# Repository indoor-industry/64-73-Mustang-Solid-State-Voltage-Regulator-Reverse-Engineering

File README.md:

A reverse engineering of the Darlington transistor based solid-state replacements for old Mustangs voltage regulators that are commonly sold as spares. 
The KiCAD project includes a schematic and a PCB with gerber files ready for production, all components are specified on the silkscreen.
These voltage regulators are not very good though, this was done out of curiosity, not necessity.

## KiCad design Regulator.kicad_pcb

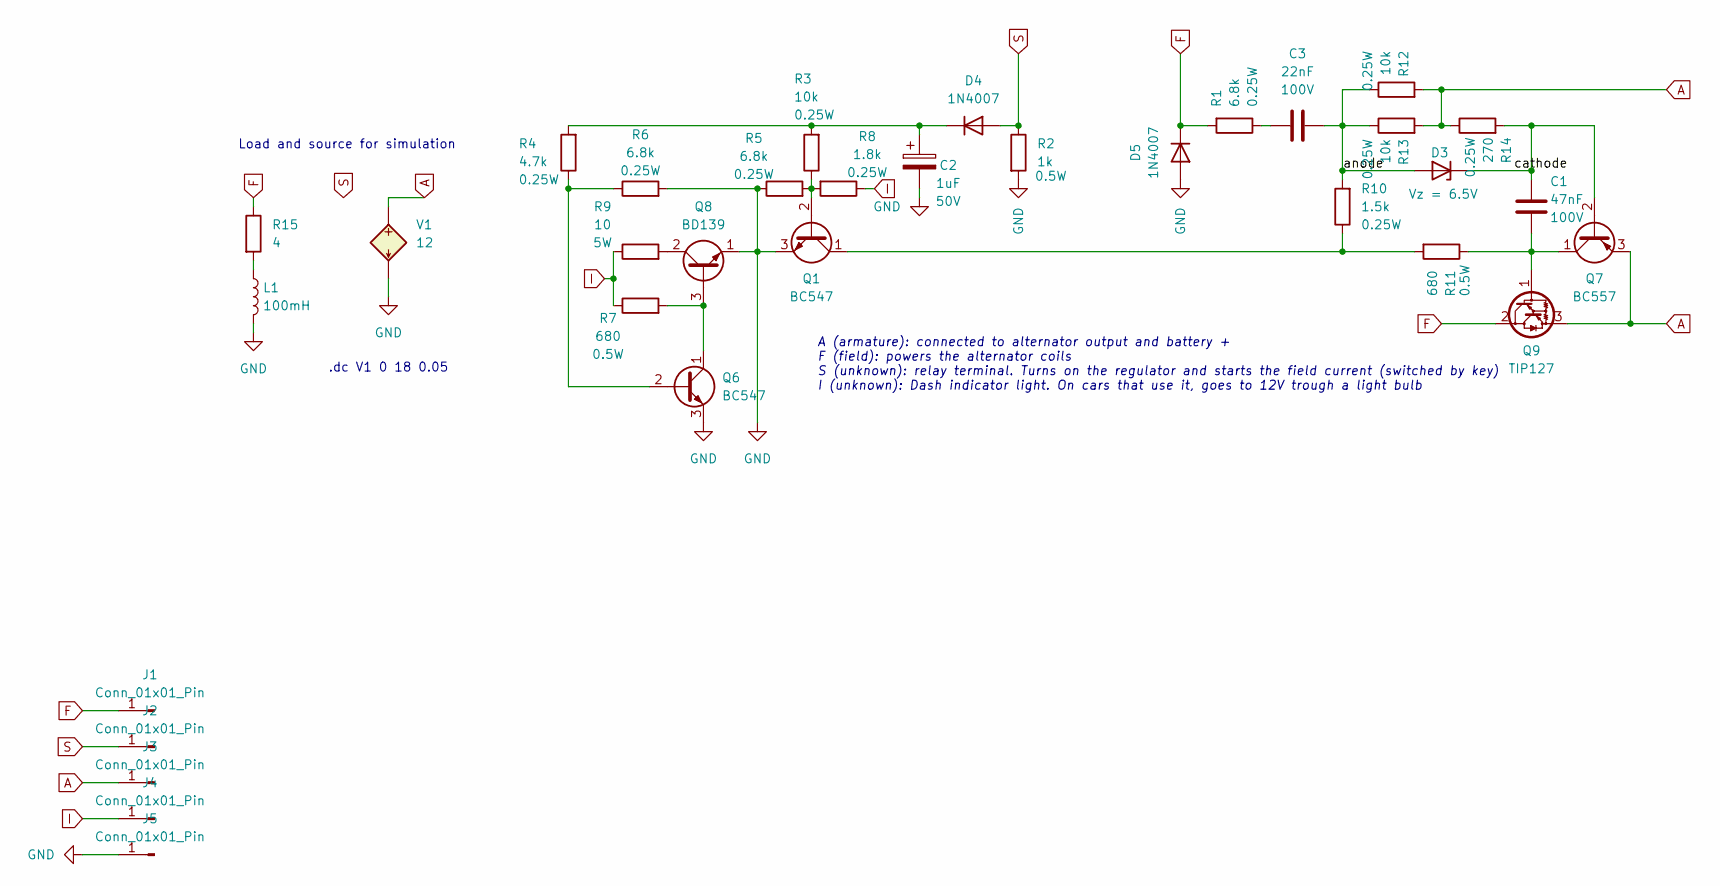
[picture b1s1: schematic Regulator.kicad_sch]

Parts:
C1: 47nF; C_Rect_L7.0mm_W2.5mm_P5.00mm
C2: 1uF; CP_Radial_D4.0mm_P2.00mm
C3: 22nF; C_Rect_L7.0mm_W2.5mm_P5.00mm
D3: Vz = 6.5V; D_A-405_P7.62mm_Horizontal
D4, D5: 1N4007; D_DO-41_SOD81_P10.16mm_Horizontal
J1, J2, J3, J4, J5: Conn_01x01_Pin; SolderWire-6sqmm_1x01_D3.5mm_OD7mm
L1: 100mH
Q1, Q6: BC547; TO-92_Inline
Q7: BC557; TO-92_Inline
Q8: BD139; TO-126-3_Vertical
Q9: TIP127; TO-220-3_Vertical
R1, R5, R6: 6.8k; R_Axial_DIN0207_L6.3mm_D2.5mm_P10.16mm_Horizontal
R2: 1k; R_Axial_DIN0309_L9.0mm_D3.2mm_P15.24mm_Horizontal
R3, R12, R13: 10k; R_Axial_DIN0207_L6.3mm_D2.5mm_P10.16mm_Horizontal
R4: 4.7k; R_Axial_DIN0207_L6.3mm_D2.5mm_P10.16mm_Horizontal
R7, R11: 680; R_Axial_DIN0309_L9.0mm_D3.2mm_P15.24mm_Horizontal
R8: 1.8k; R_Axial_DIN0207_L6.3mm_D2.5mm_P10.16mm_Horizontal
R9: 10; R_Axial_DIN0516_L15.5mm_D5.0mm_P20.32mm_Horizontal
R10: 1.5k; R_Axial_DIN0207_L6.3mm_D2.5mm_P10.16mm_Horizontal
R14: 270; R_Axial_DIN0207_L6.3mm_D2.5mm_P10.16mm_Horizontal
R15: 4
V1: 12

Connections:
/anode: C3.2, D3.2 (A), R10.2, R12.1, R13.1
/cathode: C1.1, D3.1 (K), Q7.2 (B), R14.2
A: J3.1, Q7.3 (E), Q9.3 (E), R12.2, R13.2, R14.1, V1.1 (N+)
F: D5.1 (K), J1.1, Q9.2 (C), R1.2, R15.1
GND: C2.2, D5.2 (A), J5.1, L1.2, Q1.3 (E), Q6.3 (E), Q8.1 (E), R2.2, R5.1, R6.2, V1.2 (N-)
I: J4.1, R7.1, R8.1, R9.1
unnamed: C3.1, R1.1
unnamed: C2.1, D4.1 (K), R3.2, R4.2
unnamed: L1.1, R15.2
unnamed: Q1.2 (B), R3.1, R5.2, R8.2
unnamed: Q1.1 (C), R10.1, R11.2
unnamed: Q6.2 (B), R4.1, R6.1
unnamed: Q6.1 (C), Q8.3 (B), R7.2
unnamed: C1.2, Q7.1 (C), Q9.1 (B), R11.1
unnamed: Q8.2 (C), R9.2
S: D4.2 (A), J2.1, R2.1

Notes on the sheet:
A (armature): connected to alternator output and battery + F (field): powers the alternator coils S (unknown): relay terminal. Turns on the regulator and starts the field current (switched by key) I (unknown): Dash indicator light. On cars that use it, goes to 12V trough a light bulb
Load and source for simulation
.dc V1 0 18 0.05

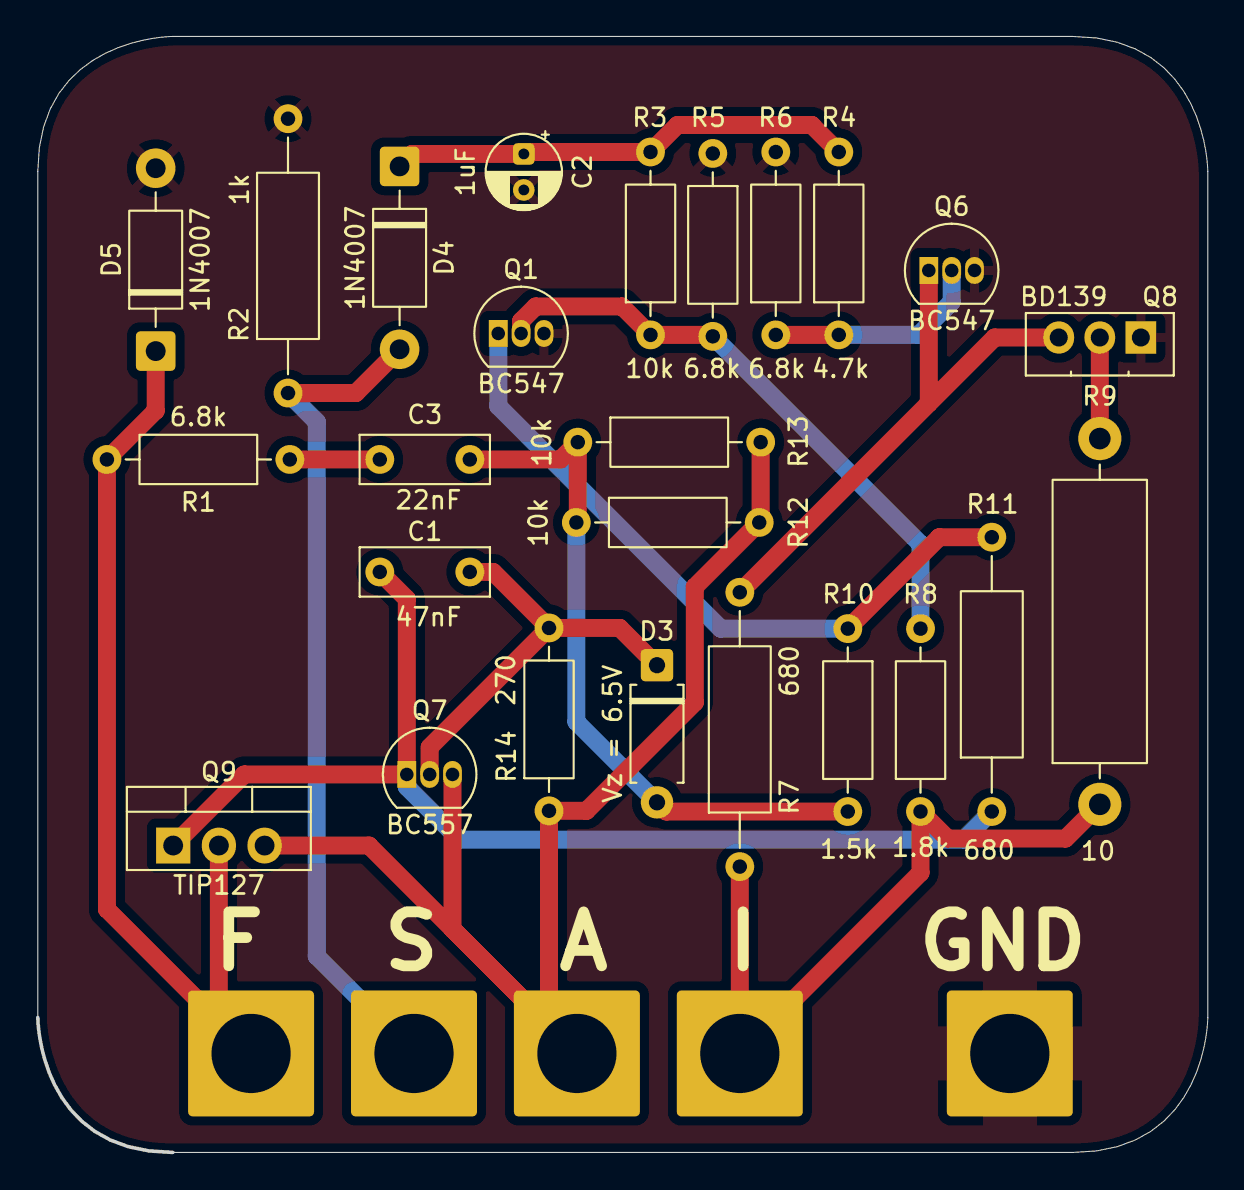
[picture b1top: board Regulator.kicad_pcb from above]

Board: 2 copper layers, 65.0 x 62.0 mm, 30 parts (0 on the bottom side), 15 nets.

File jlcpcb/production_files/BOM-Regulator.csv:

Comment,Designator,Footprint,LCSC,Quantity
BC557,Q7,TO-92_Inline,,1
10k,R3,R_Axial_DIN0207_L6.3mm_D2.5mm_P10.16mm_Horizontal,,1
BC547,Q1,TO-92_Inline,,1
1uF,C2,CP_Radial_D4.0mm_P2.00mm,,1
10k,R13,R_Axial_DIN0207_L6.3mm_D2.5mm_P10.16mm_Horizontal,,1
Conn_01x01_Pin,J1,SolderWire-6sqmm_1x01_D3.5mm_OD7mm,,1
1.8k,R8,R_Axial_DIN0207_L6.3mm_D2.5mm_P10.16mm_Horizontal,,1
Conn_01x01_Pin,J3,SolderWire-6sqmm_1x01_D3.5mm_OD7mm,,1
Vz = 6.5V,D3,D_A-405_P7.62mm_Horizontal,,1
TIP127,Q9,TO-220-3_Vertical,,1
BD139,Q8,TO-126-3_Vertical,,1
680,R7,R_Axial_DIN0309_L9.0mm_D3.2mm_P15.24mm_Horizontal,,1
6.8k,R5,R_Axial_DIN0207_L6.3mm_D2.5mm_P10.16mm_Horizontal,,1
6.8k,R6,R_Axial_DIN0207_L6.3mm_D2.5mm_P10.16mm_Horizontal,,1
1N4007,D4,D_DO-41_SOD81_P10.16mm_Horizontal,,1
10k,R12,R_Axial_DIN0207_L6.3mm_D2.5mm_P10.16mm_Horizontal,,1
Conn_01x01_Pin,J2,SolderWire-6sqmm_1x01_D3.5mm_OD7mm,,1
BC547,Q6,TO-92_Inline,,1
1k,R2,R_Axial_DIN0309_L9.0mm_D3.2mm_P15.24mm_Horizontal,,1
270,R14,R_Axial_DIN0207_L6.3mm_D2.5mm_P10.16mm_Horizontal,,1
10,R9,R_Axial_DIN0516_L15.5mm_D5.0mm_P20.32mm_Horizontal,,1
680,R11,R_Axial_DIN0309_L9.0mm_D3.2mm_P15.24mm_Horizontal,,1
1N4007,D5,D_DO-41_SOD81_P10.16mm_Horizontal,,1
6.8k,R1,R_Axial_DIN0207_L6.3mm_D2.5mm_P10.16mm_Horizontal,,1
22nF,C3,C_Rect_L7.0mm_W2.5mm_P5.00mm,,1
4.7k,R4,R_Axial_DIN0207_L6.3mm_D2.5mm_P10.16mm_Horizontal,,1
47nF,C1,C_Rect_L7.0mm_W2.5mm_P5.00mm,,1
Conn_01x01_Pin,J4,SolderWire-6sqmm_1x01_D3.5mm_OD7mm,,1
1.5k,R10,R_Axial_DIN0207_L6.3mm_D2.5mm_P10.16mm_Horizontal,,1
Conn_01x01_Pin,J5,SolderWire-6sqmm_1x01_D3.5mm_OD7mm,,1

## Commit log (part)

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2026-04-27 Routing and layout done
2026-04-29 Started simulation work for circuit
2026-05-03 Production ready prototype
